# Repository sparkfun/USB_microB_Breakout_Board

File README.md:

Breakout Board for USB microB
=============================

[  
*USB microB Breakout (BOB-09614)*](https://www.sparkfun.com/products/9614)

This breakout board gives access to a micro-B USB connector's VCC, GND, D-, and D+ pins. 

Repository Contents
-------------------
* **/Hardware** - All Eagle design files (.brd, .sch)

License Information
-------------------
The hardware is released under Creative Commons Share-alike 3.0.

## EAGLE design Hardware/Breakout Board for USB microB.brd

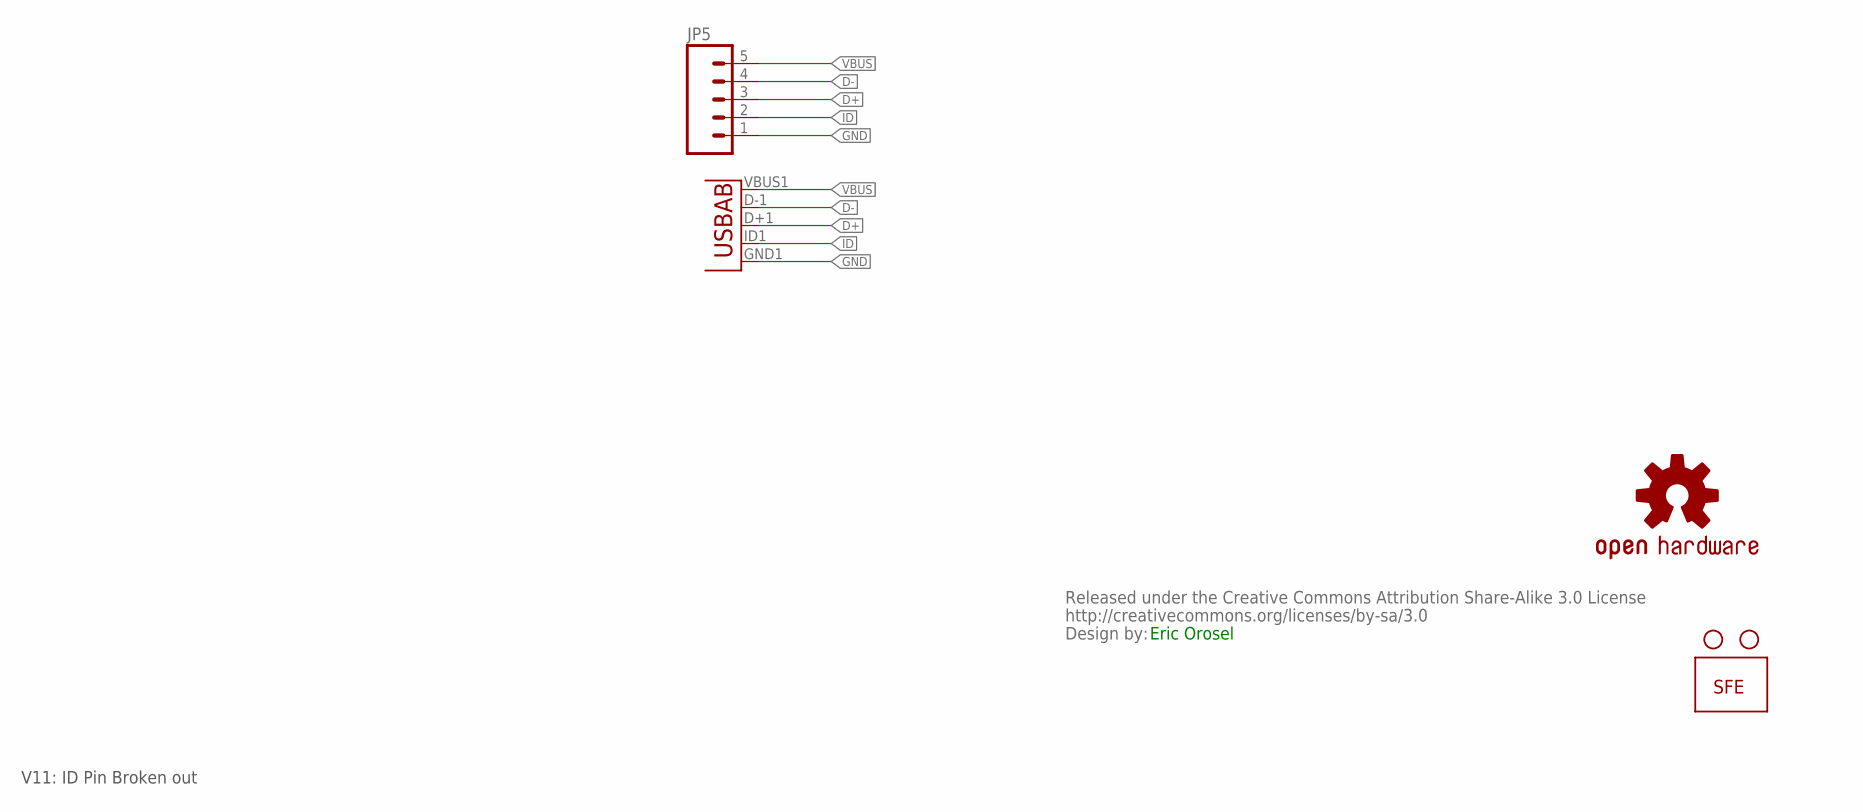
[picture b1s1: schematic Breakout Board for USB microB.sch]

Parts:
JP2: LOGO-SFESK; SFE-LOGO-FLAME
JP3, JP4: STAND-OFF
JP5: M05PTH; 1X05
U$2: CREATIVE_COMMONS
U$3: OSHW-LOGOS; OSHW-LOGO-S
U$4: MICRO_AB_USB; USB-AB-MICRO-SMD_V03

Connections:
D+: JP5.3, U$4.D+1 (D+)
D-: JP5.4, U$4.D-1 (D-)
GND: JP5.1, U$4.GND1 (GND)
ID: JP5.2, U$4.ID1 (USBID)
VBUS: JP5.5, U$4.VBUS1 (VBUS)

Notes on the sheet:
V11: ID Pin Broken out
Eric Orosel

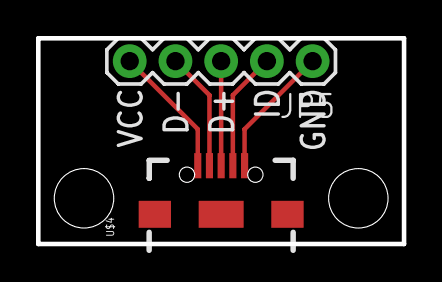
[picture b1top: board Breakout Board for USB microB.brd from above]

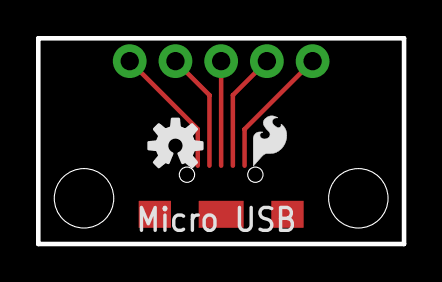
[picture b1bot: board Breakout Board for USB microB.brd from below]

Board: 2 copper layers, 20.3 x 11.4 mm, 7 parts (2 on the bottom side), 5 nets.

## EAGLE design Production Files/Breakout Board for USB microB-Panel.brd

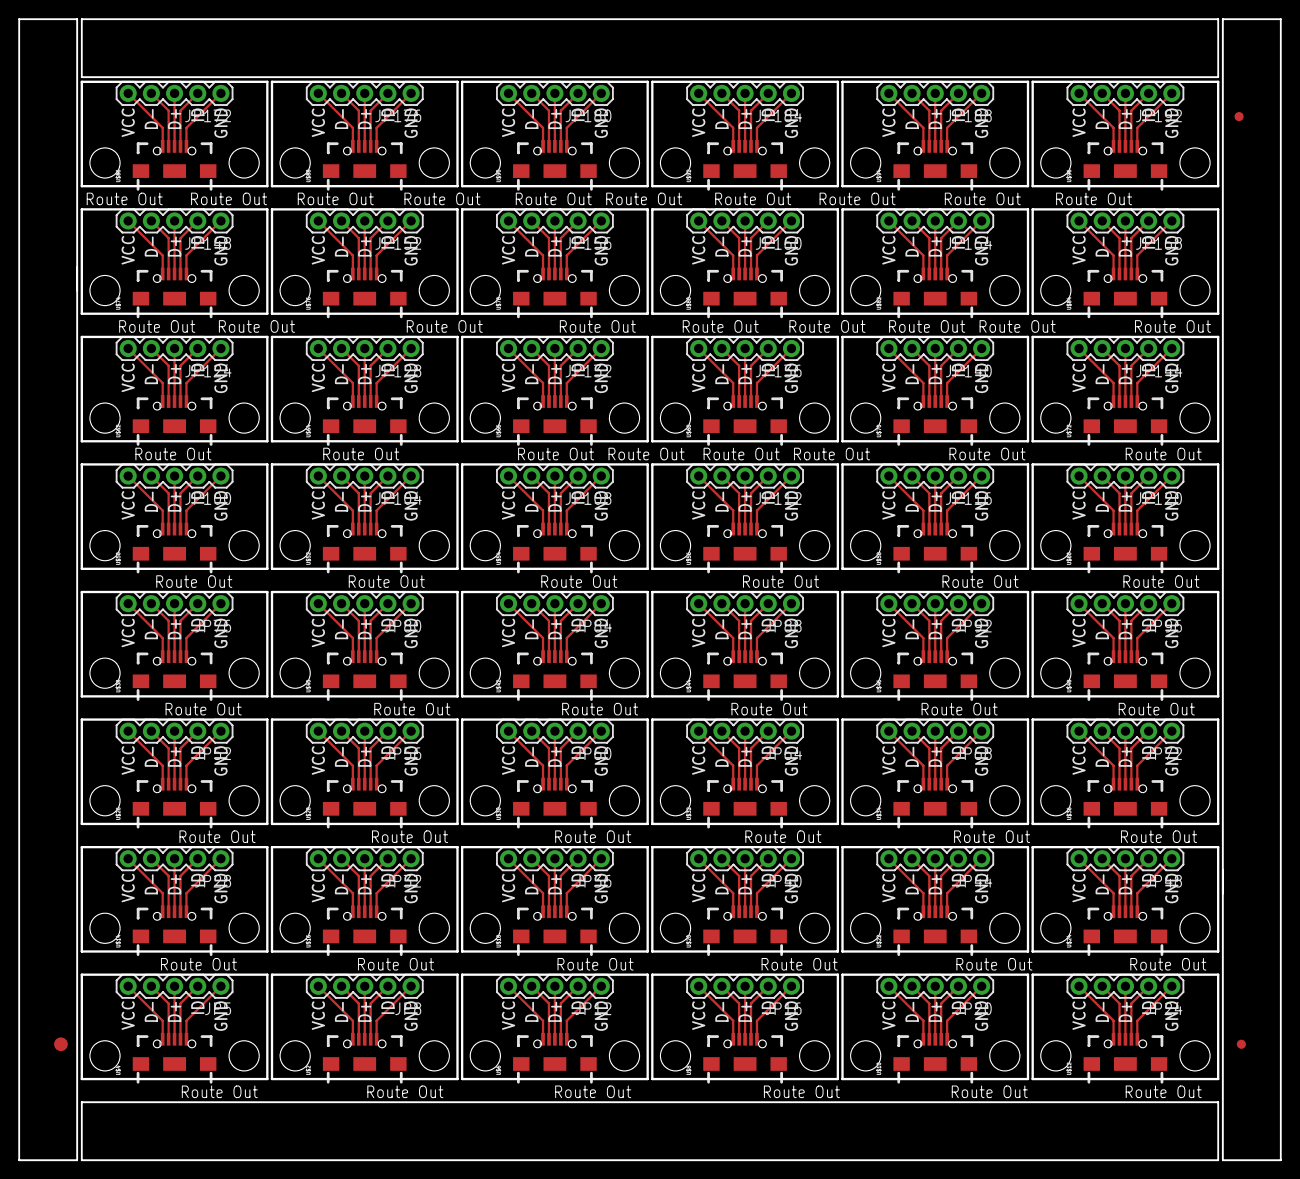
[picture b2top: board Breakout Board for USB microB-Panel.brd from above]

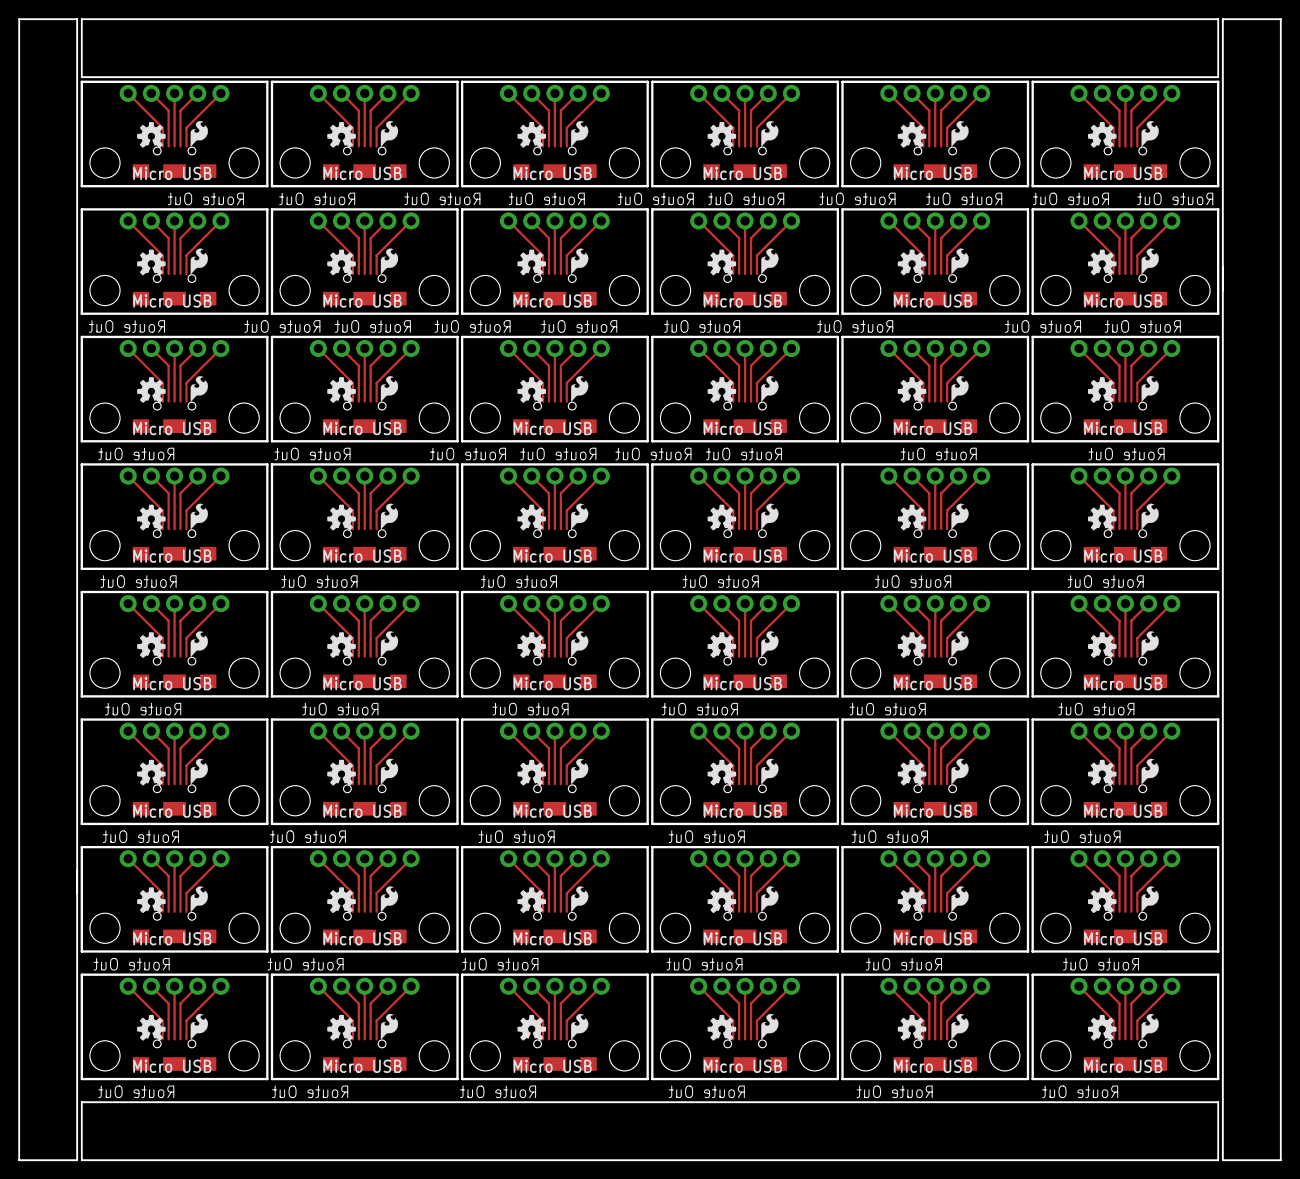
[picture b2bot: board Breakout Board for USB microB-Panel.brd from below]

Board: 2 copper layers, 138.1 x 124.9 mm, 291 parts (96 on the bottom side), 240 nets.

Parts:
E$1: FIDUCIAL-1.5X3
E$4, E$5: FIDUCIAL-1X2
JP1, JP2, JP9, JP13, JP17, JP21, JP25, JP29, JP33, JP37, JP41, JP45, JP49, JP53, JP57, JP61, JP65, JP69, JP73, JP77, JP81, JP85, JP89, JP93, JP97, JP101, JP105, JP109, JP113, JP117, JP121, JP125, JP129, JP133, JP137, JP141, JP145, JP149, JP153, JP157, JP161, JP165, JP169, JP173, JP177, JP181, JP185, JP189: LOGO-SFESK; SFE-LOGO-FLAME
JP3, JP4, JP6, JP7, JP10, JP11, JP14, JP15, JP18, JP19, JP22, JP23, JP26, JP27, JP30, JP31, JP34, JP35, JP38, JP39, JP42, JP43, JP46, JP47, JP50, JP51, JP54, JP55, JP58, JP59, JP62, JP63, JP66, JP67, JP70, JP71, JP74, JP75, JP78, JP79, JP82, JP83, JP86, JP87, JP90, JP91, JP94, JP95, JP98, JP99, JP102, JP103, JP106, JP107, JP110, JP111, JP114, JP115, JP118, JP119, JP122, JP123, JP126, JP127, JP130, JP131, JP134, JP135, JP138, JP139, JP142, JP143, JP146, JP147, JP150, JP151, JP154, JP155, JP158, JP159, JP162, JP163, JP166, JP167, JP170, JP171, JP174, JP175, JP178, JP179, JP182, JP183, JP186, JP187, JP190, JP191: STAND-OFF
JP5, JP8, JP12, JP16, JP20, JP24, JP28, JP32, JP36, JP40, JP44, JP48, JP52, JP56, JP60, JP64, JP68, JP72, JP76, JP80, JP84, JP88, JP92, JP96, JP100, JP104, JP108, JP112, JP116, JP120, JP124, JP128, JP132, JP136, JP140, JP144, JP148, JP152, JP156, JP160, JP164, JP168, JP172, JP176, JP180, JP184, JP188, JP192: 1X05
U$1, U$3, U$5, U$7, U$9, U$11, U$13, U$15, U$17, U$19, U$21, U$23, U$25, U$27, U$29, U$31, U$33, U$35, U$37, U$39, U$41, U$43, U$45, U$47, U$49, U$51, U$53, U$55, U$57, U$59, U$61, U$63, U$65, U$67, U$69, U$71, U$73, U$75, U$77, U$79, U$81, U$83, U$85, U$87, U$89, U$91, U$93, U$95: OSHW-LOGOS; OSHW-LOGO-S
U$2, U$4, U$6, U$8, U$10, U$12, U$14, U$16, U$18, U$20, U$22, U$24, U$26, U$28, U$30, U$32, U$34, U$36, U$38, U$40, U$42, U$44, U$46, U$48, U$50, U$52, U$54, U$56, U$58, U$60, U$62, U$64, U$66, U$68, U$70, U$72, U$74, U$76, U$78, U$80, U$82, U$84, U$86, U$88, U$90, U$92, U$94, U$96: USB-AB-MICRO-SMD_V02_BOSS

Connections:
D+: JP5.3, U$4.D+1
D+1: JP8.3, U$2.D+1
D+2: JP12.3, U$6.D+1
D+3: JP16.3, U$8.D+1
D+4: JP20.3, U$10.D+1
D+5: JP24.3, U$12.D+1
D+6: JP28.3, U$14.D+1
D+7: JP32.3, U$16.D+1
D+8: JP36.3, U$18.D+1
D+9: JP40.3, U$20.D+1
D+10: JP44.3, U$22.D+1
D+11: JP48.3, U$24.D+1
D+12: JP52.3, U$26.D+1
D+13: JP56.3, U$28.D+1
D+14: JP60.3, U$30.D+1
D+15: JP64.3, U$32.D+1
D+16: JP68.3, U$34.D+1
D+17: JP72.3, U$36.D+1
D+18: JP76.3, U$38.D+1
D+19: JP80.3, U$40.D+1
D+20: JP84.3, U$42.D+1
D+21: JP88.3, U$44.D+1
D+22: JP92.3, U$46.D+1
D+23: JP96.3, U$48.D+1
D+24: JP100.3, U$50.D+1
D+25: JP104.3, U$52.D+1
D+26: JP108.3, U$54.D+1
D+27: JP112.3, U$56.D+1
D+28: JP116.3, U$58.D+1
D+29: JP120.3, U$60.D+1
D+30: JP124.3, U$62.D+1
D+31: JP128.3, U$64.D+1
D+32: JP132.3, U$66.D+1
D+33: JP136.3, U$68.D+1
D+34: JP140.3, U$70.D+1
D+35: JP144.3, U$72.D+1
D+36: JP148.3, U$74.D+1
D+37: JP152.3, U$76.D+1
D+38: JP156.3, U$78.D+1
D+39: JP160.3, U$80.D+1
D+40: JP164.3, U$82.D+1
D+41: JP168.3, U$84.D+1
D+42: JP172.3, U$86.D+1
D+43: JP176.3, U$88.D+1
D+44: JP180.3, U$90.D+1
D+45: JP184.3, U$92.D+1
D+46: JP188.3, U$94.D+1
D+47: JP192.3, U$96.D+1
D-: JP5.4, U$4.D-1
D-1: JP8.4, U$2.D-1
D-2: JP12.4, U$6.D-1
D-3: JP16.4, U$8.D-1
D-4: JP20.4, U$10.D-1
D-5: JP24.4, U$12.D-1
D-6: JP28.4, U$14.D-1
D-7: JP32.4, U$16.D-1
D-8: JP36.4, U$18.D-1
D-9: JP40.4, U$20.D-1
D-10: JP44.4, U$22.D-1
D-11: JP48.4, U$24.D-1
D-12: JP52.4, U$26.D-1
D-13: JP56.4, U$28.D-1
D-14: JP60.4, U$30.D-1
D-15: JP64.4, U$32.D-1
D-16: JP68.4, U$34.D-1
D-17: JP72.4, U$36.D-1
D-18: JP76.4, U$38.D-1
D-19: JP80.4, U$40.D-1
D-20: JP84.4, U$42.D-1
D-21: JP88.4, U$44.D-1
D-22: JP92.4, U$46.D-1
D-23: JP96.4, U$48.D-1
D-24: JP100.4, U$50.D-1
D-25: JP104.4, U$52.D-1
D-26: JP108.4, U$54.D-1
D-27: JP112.4, U$56.D-1
D-28: JP116.4, U$58.D-1
D-29: JP120.4, U$60.D-1
D-30: JP124.4, U$62.D-1
D-31: JP128.4, U$64.D-1
D-32: JP132.4, U$66.D-1
D-33: JP136.4, U$68.D-1
D-34: JP140.4, U$70.D-1
D-35: JP144.4, U$72.D-1
D-36: JP148.4, U$74.D-1
D-37: JP152.4, U$76.D-1
D-38: JP156.4, U$78.D-1
D-39: JP160.4, U$80.D-1
D-40: JP164.4, U$82.D-1
D-41: JP168.4, U$84.D-1
D-42: JP172.4, U$86.D-1
D-43: JP176.4, U$88.D-1
D-44: JP180.4, U$90.D-1
D-45: JP184.4, U$92.D-1
D-46: JP188.4, U$94.D-1
D-47: JP192.4, U$96.D-1
GND: JP5.1, U$4.GND1
GND1: JP8.1, U$2.GND1
GND2: JP12.1, U$6.GND1
GND3: JP16.1, U$8.GND1
GND4: JP20.1, U$10.GND1
GND5: JP24.1, U$12.GND1
GND6: JP28.1, U$14.GND1
GND7: JP32.1, U$16.GND1
GND8: JP36.1, U$18.GND1
GND9: JP40.1, U$20.GND1
GND10: JP44.1, U$22.GND1
GND11: JP48.1, U$24.GND1
GND12: JP52.1, U$26.GND1
GND13: JP56.1, U$28.GND1
GND14: JP60.1, U$30.GND1
GND15: JP64.1, U$32.GND1
GND16: JP68.1, U$34.GND1
GND17: JP72.1, U$36.GND1
GND18: JP76.1, U$38.GND1
GND19: JP80.1, U$40.GND1
GND20: JP84.1, U$42.GND1
GND21: JP88.1, U$44.GND1
GND22: JP92.1, U$46.GND1
GND23: JP96.1, U$48.GND1
GND24: JP100.1, U$50.GND1
GND25: JP104.1, U$52.GND1
GND26: JP108.1, U$54.GND1
GND27: JP112.1, U$56.GND1
GND28: JP116.1, U$58.GND1
GND29: JP120.1, U$60.GND1
GND30: JP124.1, U$62.GND1
GND31: JP128.1, U$64.GND1
GND32: JP132.1, U$66.GND1
GND33: JP136.1, U$68.GND1
GND34: JP140.1, U$70.GND1
GND35: JP144.1, U$72.GND1
GND36: JP148.1, U$74.GND1
GND37: JP152.1, U$76.GND1
GND38: JP156.1, U$78.GND1
GND39: JP160.1, U$80.GND1
GND40: JP164.1, U$82.GND1
GND41: JP168.1, U$84.GND1
GND42: JP172.1, U$86.GND1
GND43: JP176.1, U$88.GND1
GND44: JP180.1, U$90.GND1
GND45: JP184.1, U$92.GND1
GND46: JP188.1, U$94.GND1
GND47: JP192.1, U$96.GND1
ID: JP5.2, U$4.ID1
ID1: JP8.2, U$2.ID1
ID2: JP12.2, U$6.ID1
ID3: JP16.2, U$8.ID1
ID4: JP20.2, U$10.ID1
ID5: JP24.2, U$12.ID1
ID6: JP28.2, U$14.ID1
ID7: JP32.2, U$16.ID1
ID8: JP36.2, U$18.ID1
ID9: JP40.2, U$20.ID1
ID10: JP44.2, U$22.ID1
ID11: JP48.2, U$24.ID1
ID12: JP52.2, U$26.ID1
ID13: JP56.2, U$28.ID1
ID14: JP60.2, U$30.ID1
ID15: JP64.2, U$32.ID1
ID16: JP68.2, U$34.ID1
ID17: JP72.2, U$36.ID1
ID18: JP76.2, U$38.ID1
ID19: JP80.2, U$40.ID1
ID20: JP84.2, U$42.ID1
ID21: JP88.2, U$44.ID1
ID22: JP92.2, U$46.ID1
ID23: JP96.2, U$48.ID1
ID24: JP100.2, U$50.ID1
ID25: JP104.2, U$52.ID1
ID26: JP108.2, U$54.ID1
ID27: JP112.2, U$56.ID1
ID28: JP116.2, U$58.ID1
ID29: JP120.2, U$60.ID1
ID30: JP124.2, U$62.ID1
ID31: JP128.2, U$64.ID1
ID32: JP132.2, U$66.ID1
ID33: JP136.2, U$68.ID1
ID34: JP140.2, U$70.ID1
ID35: JP144.2, U$72.ID1
ID36: JP148.2, U$74.ID1
ID37: JP152.2, U$76.ID1
ID38: JP156.2, U$78.ID1
ID39: JP160.2, U$80.ID1
ID40: JP164.2, U$82.ID1
ID41: JP168.2, U$84.ID1
ID42: JP172.2, U$86.ID1
ID43: JP176.2, U$88.ID1
ID44: JP180.2, U$90.ID1
ID45: JP184.2, U$92.ID1
ID46: JP188.2, U$94.ID1
ID47: JP192.2, U$96.ID1
VBUS: JP5.5, U$4.VBUS1
VBUS1: JP8.5, U$2.VBUS1
VBUS2: JP12.5, U$6.VBUS1
VBUS3: JP16.5, U$8.VBUS1
VBUS4: JP20.5, U$10.VBUS1
VBUS5: JP24.5, U$12.VBUS1
VBUS6: JP28.5, U$14.VBUS1
VBUS7: JP32.5, U$16.VBUS1
VBUS8: JP36.5, U$18.VBUS1
VBUS9: JP40.5, U$20.VBUS1
VBUS10: JP44.5, U$22.VBUS1
VBUS11: JP48.5, U$24.VBUS1
VBUS12: JP52.5, U$26.VBUS1
VBUS13: JP56.5, U$28.VBUS1
VBUS14: JP60.5, U$30.VBUS1
VBUS15: JP64.5, U$32.VBUS1
VBUS16: JP68.5, U$34.VBUS1
VBUS17: JP72.5, U$36.VBUS1
VBUS18: JP76.5, U$38.VBUS1
VBUS19: JP80.5, U$40.VBUS1
VBUS20: JP84.5, U$42.VBUS1
VBUS21: JP88.5, U$44.VBUS1
VBUS22: JP92.5, U$46.VBUS1
VBUS23: JP96.5, U$48.VBUS1
VBUS24: JP100.5, U$50.VBUS1
VBUS25: JP104.5, U$52.VBUS1
VBUS26: JP108.5, U$54.VBUS1
VBUS27: JP112.5, U$56.VBUS1
VBUS28: JP116.5, U$58.VBUS1
VBUS29: JP120.5, U$60.VBUS1
VBUS30: JP124.5, U$62.VBUS1
VBUS31: JP128.5, U$64.VBUS1
VBUS32: JP132.5, U$66.VBUS1
VBUS33: JP136.5, U$68.VBUS1
VBUS34: JP140.5, U$70.VBUS1
VBUS35: JP144.5, U$72.VBUS1
VBUS36: JP148.5, U$74.VBUS1
VBUS37: JP152.5, U$76.VBUS1
VBUS38: JP156.5, U$78.VBUS1
VBUS39: JP160.5, U$80.VBUS1
VBUS40: JP164.5, U$82.VBUS1
VBUS41: JP168.5, U$84.VBUS1
VBUS42: JP172.5, U$86.VBUS1
VBUS43: JP176.5, U$88.VBUS1
VBUS44: JP180.5, U$90.VBUS1
VBUS45: JP184.5, U$92.VBUS1
VBUS46: JP188.5, U$94.VBUS1
VBUS47: JP192.5, U$96.VBUS1

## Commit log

2013-05-20 Add hardware files
    Added "ID" pin to breakout. Updated package on connector to use mounting
    pads (underneath connector)
2013-08-19 Swapped in new microB FP w/ bosses
2013-08-20 Minor sch. clean-up
2013-10-02 Panel Created
2015-02-04 Updated board with current FP.
    No changes to layout just part value update. Engineering file audit. See
    eagle issues for more info.
2017-08-07 Input Value
    Added value to MICRO AB USB component for 3D Modeling
2025-06-27 Update README.md
    Updating link

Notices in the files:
parts and their libraries:
SparkFun-Aesthetics: Licensing: CC v3.0 Share-Alike You are welcome to use this library for commercial purposes.
SparkFun-Aesthetics: Released under the Creative Commons Attribution Share-Alike 3.0 License
SparkFun-Aesthetics: http://creativecommons.org/licenses/by-sa/3.0
